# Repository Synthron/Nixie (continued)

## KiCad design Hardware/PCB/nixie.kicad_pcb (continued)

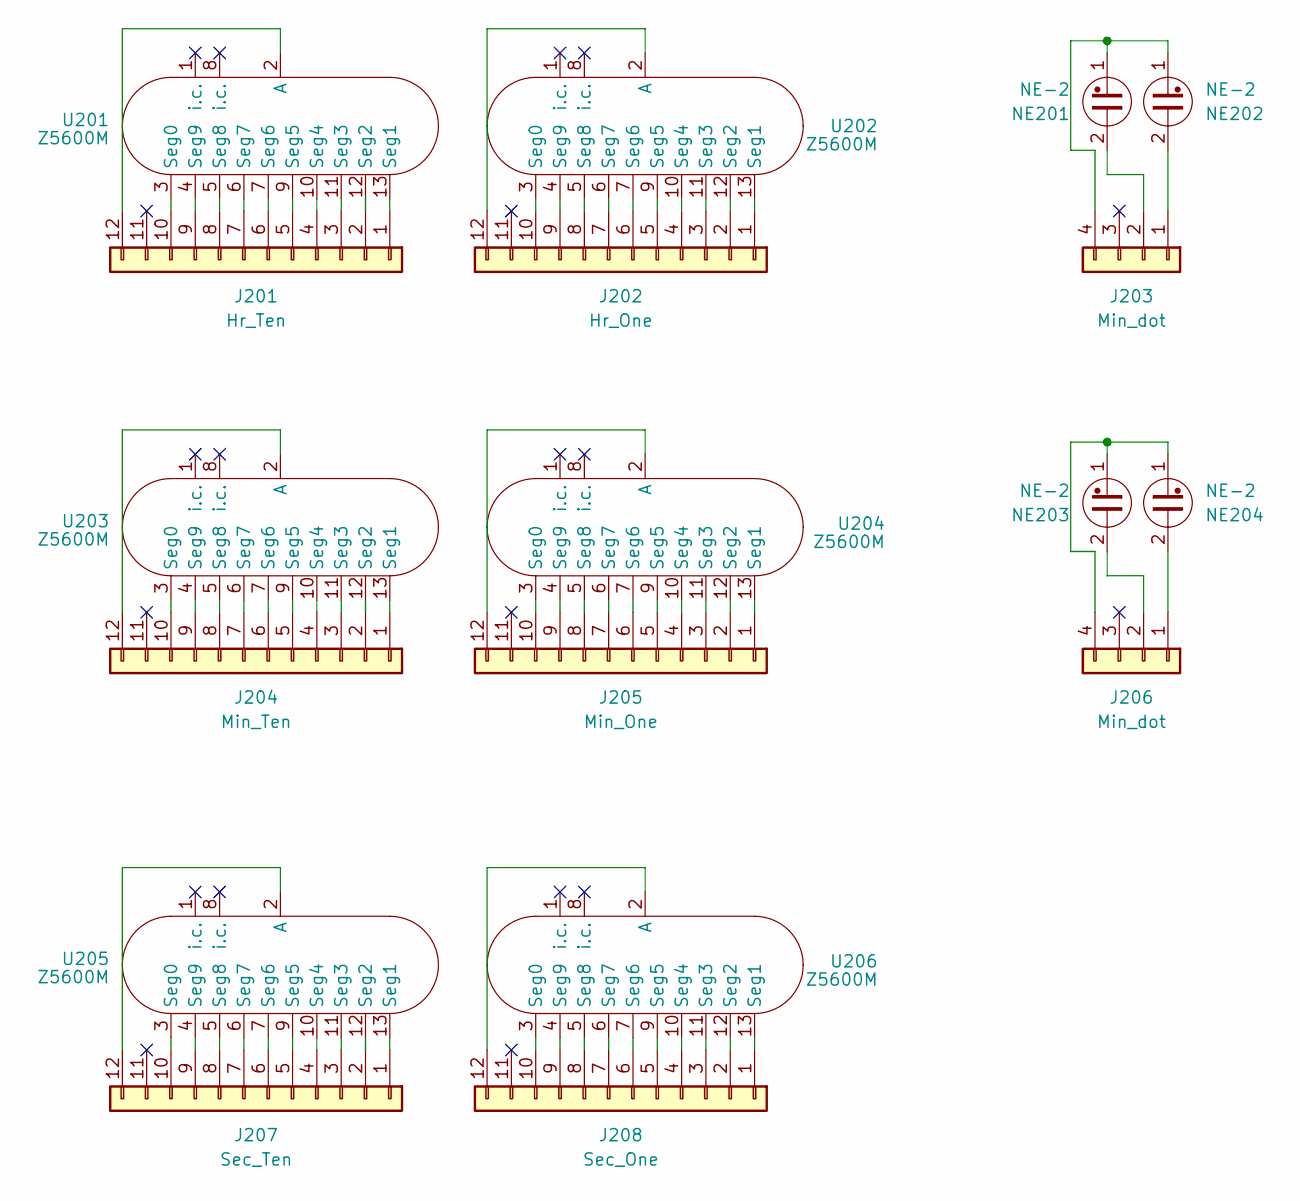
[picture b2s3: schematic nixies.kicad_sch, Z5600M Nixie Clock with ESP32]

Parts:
J201: Hr_Ten; PinSocket_1x12_P2.54mm_Vertical
J202: Hr_One; PinSocket_1x12_P2.54mm_Vertical
J203, J206: Min_dot; PinSocket_1x04_P2.54mm_Vertical
J204: Min_Ten; PinSocket_1x12_P2.54mm_Vertical
J205: Min_One; PinSocket_1x12_P2.54mm_Vertical
J207: Sec_Ten; PinSocket_1x12_P2.54mm_Vertical
J208: Sec_One; PinSocket_1x12_P2.54mm_Vertical
NE201, NE202, NE203, NE204: NE-2; Valve_Glimm
U201, U202, U203, U204, U205, U206: Z5600M; B13B

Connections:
unnamed: J201.1, U201.13 (Seg1)
unnamed: J201.2, U201.12 (Seg2)
unnamed: J201.3, U201.11 (Seg3)
unnamed: J201.4, U201.10 (Seg4)
unnamed: J201.5, U201.9 (Seg5)
unnamed: J201.6, U201.7 (Seg6)
unnamed: J201.7, U201.6 (Seg7)
unnamed: J201.8, U201.5 (Seg8)
unnamed: J201.9, U201.4 (Seg9)
unnamed: J201.10, U201.3 (Seg0)
unnamed: J201.12, U201.2 (A)
unnamed: J202.1, U202.13 (Seg1)
unnamed: J202.2, U202.12 (Seg2)
unnamed: J202.3, U202.11 (Seg3)
unnamed: J202.4, U202.10 (Seg4)
unnamed: J202.5, U202.9 (Seg5)
unnamed: J202.6, U202.7 (Seg6)
unnamed: J202.7, U202.6 (Seg7)
unnamed: J202.8, U202.5 (Seg8)
unnamed: J202.9, U202.4 (Seg9)
unnamed: J202.10, U202.3 (Seg0)
unnamed: J202.12, U202.2 (A)
unnamed: J203.1, NE202.2
unnamed: J203.2, NE201.2
unnamed: J203.4, NE201.1, NE202.1
unnamed: J204.1, U203.13 (Seg1)
unnamed: J204.2, U203.12 (Seg2)
unnamed: J204.3, U203.11 (Seg3)
unnamed: J204.4, U203.10 (Seg4)
unnamed: J204.5, U203.9 (Seg5)
unnamed: J204.6, U203.7 (Seg6)
unnamed: J204.7, U203.6 (Seg7)
unnamed: J204.8, U203.5 (Seg8)
unnamed: J204.9, U203.4 (Seg9)
unnamed: J204.10, U203.3 (Seg0)
unnamed: J204.12, U203.2 (A)
unnamed: J205.1, U204.13 (Seg1)
unnamed: J205.2, U204.12 (Seg2)
unnamed: J205.3, U204.11 (Seg3)
unnamed: J205.4, U204.10 (Seg4)
unnamed: J205.5, U204.9 (Seg5)
unnamed: J205.6, U204.7 (Seg6)
unnamed: J205.7, U204.6 (Seg7)
unnamed: J205.8, U204.5 (Seg8)
unnamed: J205.9, U204.4 (Seg9)
unnamed: J205.10, U204.3 (Seg0)
unnamed: J205.12, U204.2 (A)
unnamed: J206.1, NE204.2
unnamed: J206.2, NE203.2
unnamed: J206.4, NE203.1, NE204.1
unnamed: J207.1, U205.13 (Seg1)
unnamed: J207.2, U205.12 (Seg2)
unnamed: J207.3, U205.11 (Seg3)
unnamed: J207.4, U205.10 (Seg4)
unnamed: J207.5, U205.9 (Seg5)
unnamed: J207.6, U205.7 (Seg6)
unnamed: J207.7, U205.6 (Seg7)
unnamed: J207.8, U205.5 (Seg8)
unnamed: J207.9, U205.4 (Seg9)
unnamed: J207.10, U205.3 (Seg0)
unnamed: J207.12, U205.2 (A)
unnamed: J208.1, U206.13 (Seg1)
unnamed: J208.2, U206.12 (Seg2)
unnamed: J208.3, U206.11 (Seg3)
unnamed: J208.4, U206.10 (Seg4)
unnamed: J208.5, U206.9 (Seg5)
unnamed: J208.6, U206.7 (Seg6)
unnamed: J208.7, U206.6 (Seg7)
unnamed: J208.8, U206.5 (Seg8)
unnamed: J208.9, U206.4 (Seg9)
unnamed: J208.10, U206.3 (Seg0)
unnamed: J208.12, U206.2 (A)

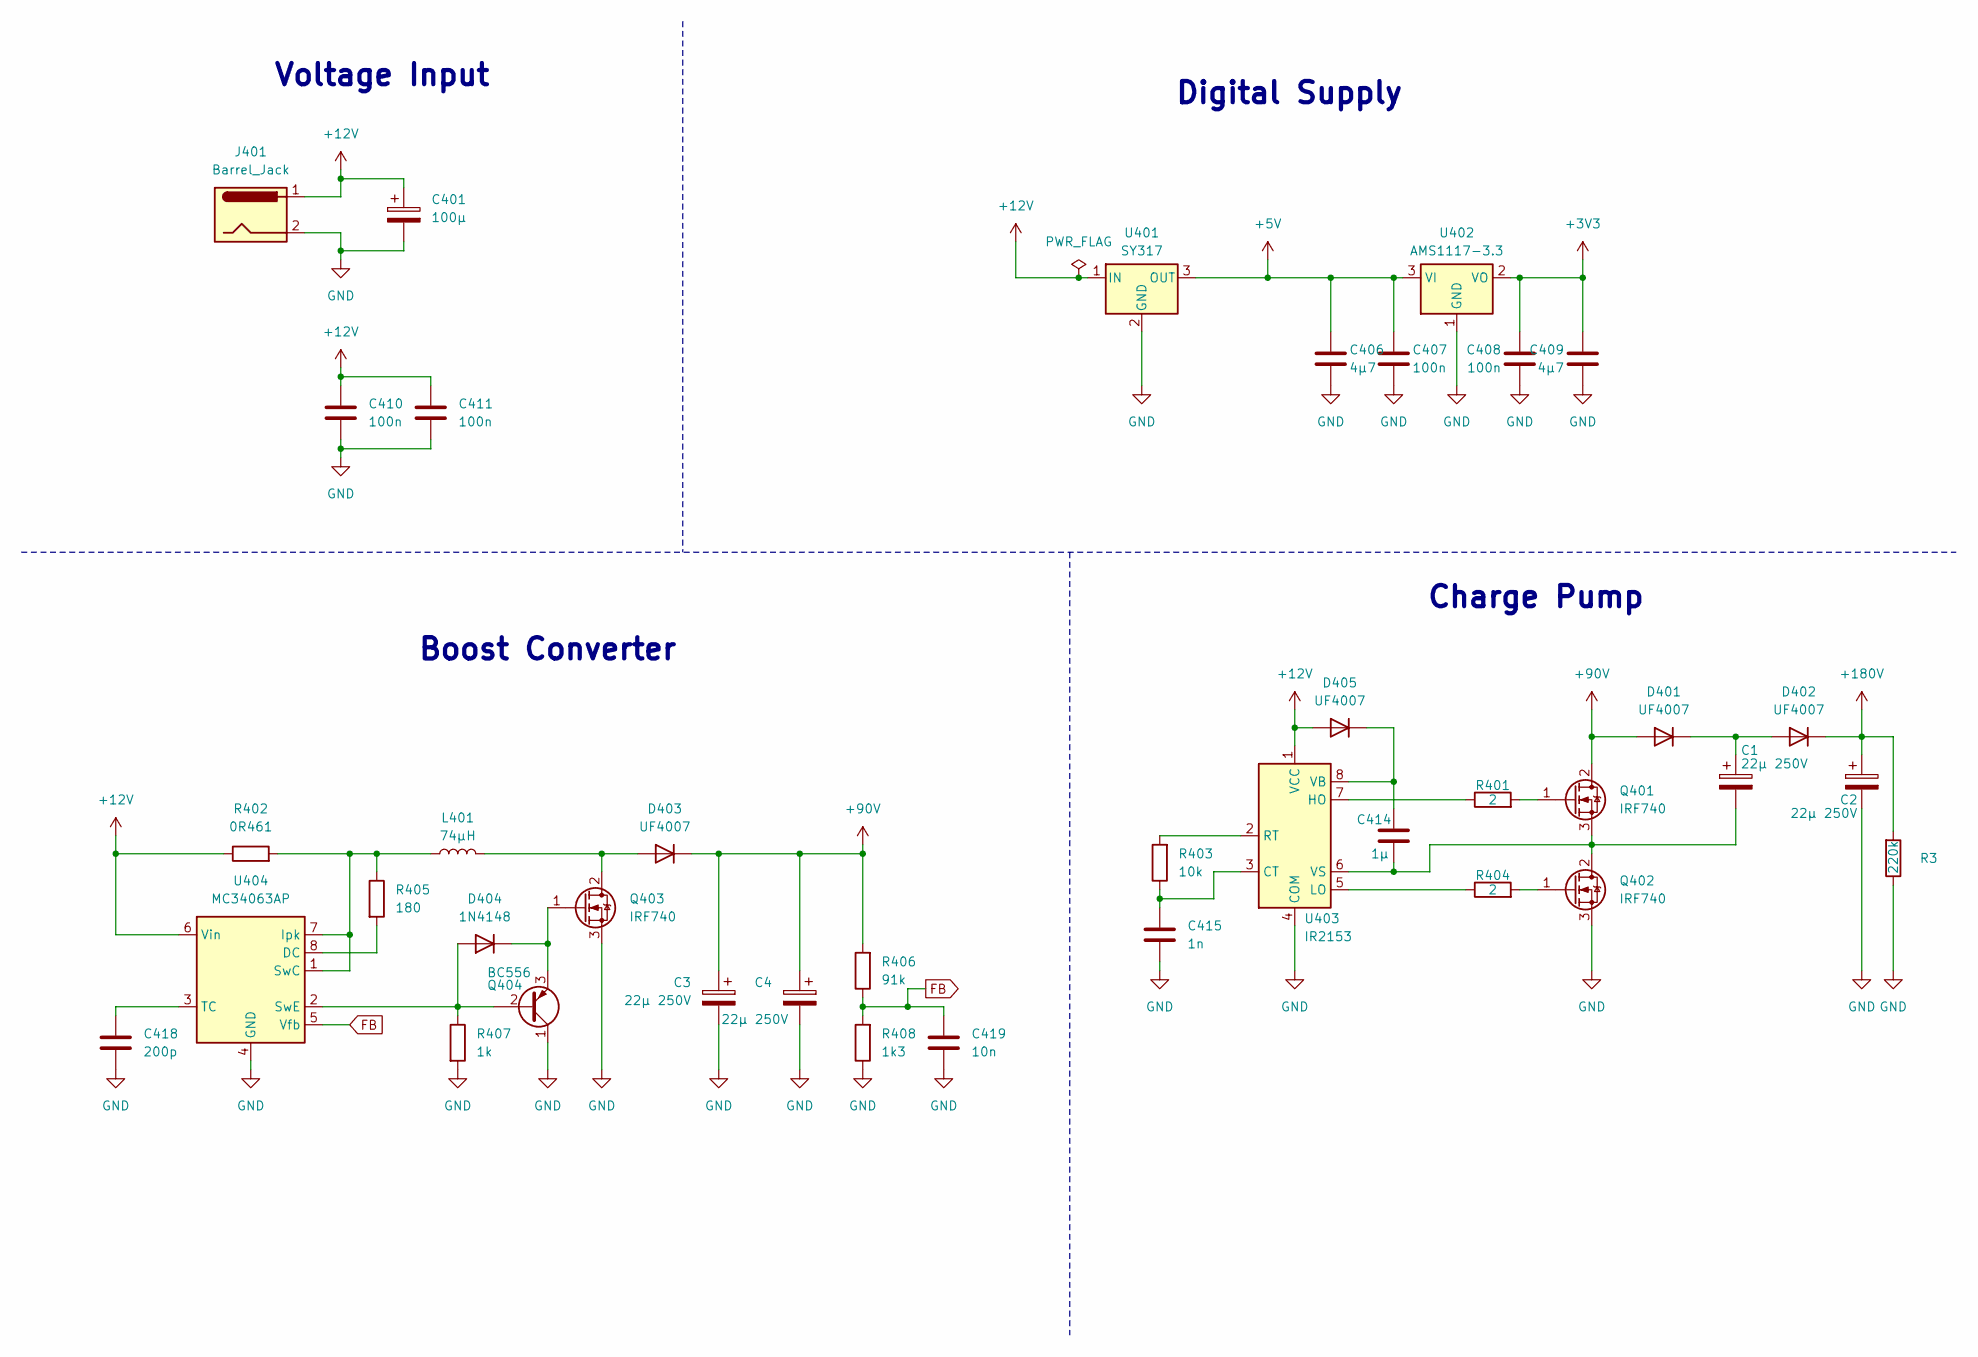
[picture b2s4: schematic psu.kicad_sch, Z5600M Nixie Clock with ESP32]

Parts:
C1, C2, C3, C4: 22µ 250V; CP_Radial_D10.0mm_P5.00mm
C401: 100µ; CP_Radial_D5.0mm_P2.50mm
C406, C409: 4µ7; C_0805_2012Metric
C407, C408: 100n; C_0805_2012Metric
C410, C411: 100n; C_Disc_D3.0mm_W1.6mm_P2.50mm
C414: 1µ; C_Rect_L18.0mm_W8.0mm_P15.00mm_FKS3_FKP3
C415: 1n; C_Disc_D3.0mm_W1.6mm_P2.50mm
C418: 200p; C_Disc_D3.0mm_W1.6mm_P2.50mm
C419: 10n; C_Disc_D3.0mm_W1.6mm_P2.50mm
D401, D402, D403, D405: UF4007; D_DO-41_SOD81_P10.16mm_Horizontal
D404: 1N4148; D_DO-35_SOD27_P7.62mm_Horizontal
J401: Barrel_Jack; BarrelJack_Horizontal
L401: 74µH; FT50-43
Q401, Q402, Q403: IRF740; TO-220-3_Vertical
Q404: BC556; TO-92
R3: 220k; R_Axial_DIN0207_L6.3mm_D2.5mm_P2.54mm_Vertical
R401, R404: 2; R_Axial_DIN0207_L6.3mm_D2.5mm_P2.54mm_Vertical
R402: 0R461; R_Axial_DIN0614_L14.3mm_D5.7mm_P5.08mm_Vertical
R403: 10k; R_Axial_DIN0207_L6.3mm_D2.5mm_P2.54mm_Vertical
R405: 180; R_Axial_DIN0207_L6.3mm_D2.5mm_P2.54mm_Vertical
R406: 91k; R_Axial_DIN0207_L6.3mm_D2.5mm_P2.54mm_Vertical
R407: 1k; R_Axial_DIN0207_L6.3mm_D2.5mm_P2.54mm_Vertical
R408: 1k3; R_Axial_DIN0207_L6.3mm_D2.5mm_P2.54mm_Vertical
U401: SY317; TO-220-3_Vertical
U402: AMS1117-3.3; SOT-223-3_TabPin2
U403: IR2153; DIP-8_W7.62mm
U404: MC34063AP; DIP-8_W7.62mm

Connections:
+3V3: C408.1, C409.1, U402.2 (VO); also elsewhere on the board
+5V: C406.1, C407.1, U401.3 (OUT), U402.3 (VI); also elsewhere on the board
+12V: C401.1, C410.1, C411.1, D405.2 (A), J401.1, R402.1, U401.1 (IN), U403.1 (VCC), U404.6 (Vin)
+90V: C3.1, C4.1, D401.2 (A), D403.1 (K), Q401.2 (D), R406.2
+180V: C2.1, D402.1 (K), R3.2; also elsewhere on the board
FB: C419.1, R406.1, R408.2, U404.5 (Vfb)
GND: C2.2, C3.2, C4.2, C401.2, C406.2, C407.2, C408.2, C409.2, C410.2, C411.2, C415.2, C418.2, C419.2, J401.2, Q402.3 (S), Q403.3 (S), Q404.1 (C), R3.1, R407.2, R408.1, U401.2 (GND), U402.1 (GND), U403.4 (COM), U404.4 (GND); also elsewhere on the board
unnamed: C1.1, D401.1 (K), D402.2 (A)
unnamed: D403.2 (A), L401.2, Q403.2 (D)
unnamed: D404.2 (A), Q404.2 (B), R407.1, U404.2 (SwE)
unnamed: D404.1 (K), Q403.1 (G), Q404.3 (E)
unnamed: C414.1, D405.1 (K), U403.8 (VB)
unnamed: Q401.1 (G), R401.2
unnamed: C1.2, C414.2, Q401.3 (S), Q402.2 (D), U403.6 (VS)
unnamed: Q402.1 (G), R404.2
unnamed: C415.1, R403.1, U403.3 (CT)
unnamed: R401.1, U403.7 (HO)
unnamed: R404.1, U403.5 (LO)
unnamed: R403.2, U403.2 (RT)
unnamed: R405.2, U404.8 (DC)
unnamed: L401.1, R402.2, R405.1, U404.1 (SwC), U404.7 (Ipk)
unnamed: C418.1, U404.3 (TC)

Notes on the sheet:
Digital Supply
Boost Converter
Charge Pump
Voltage Input

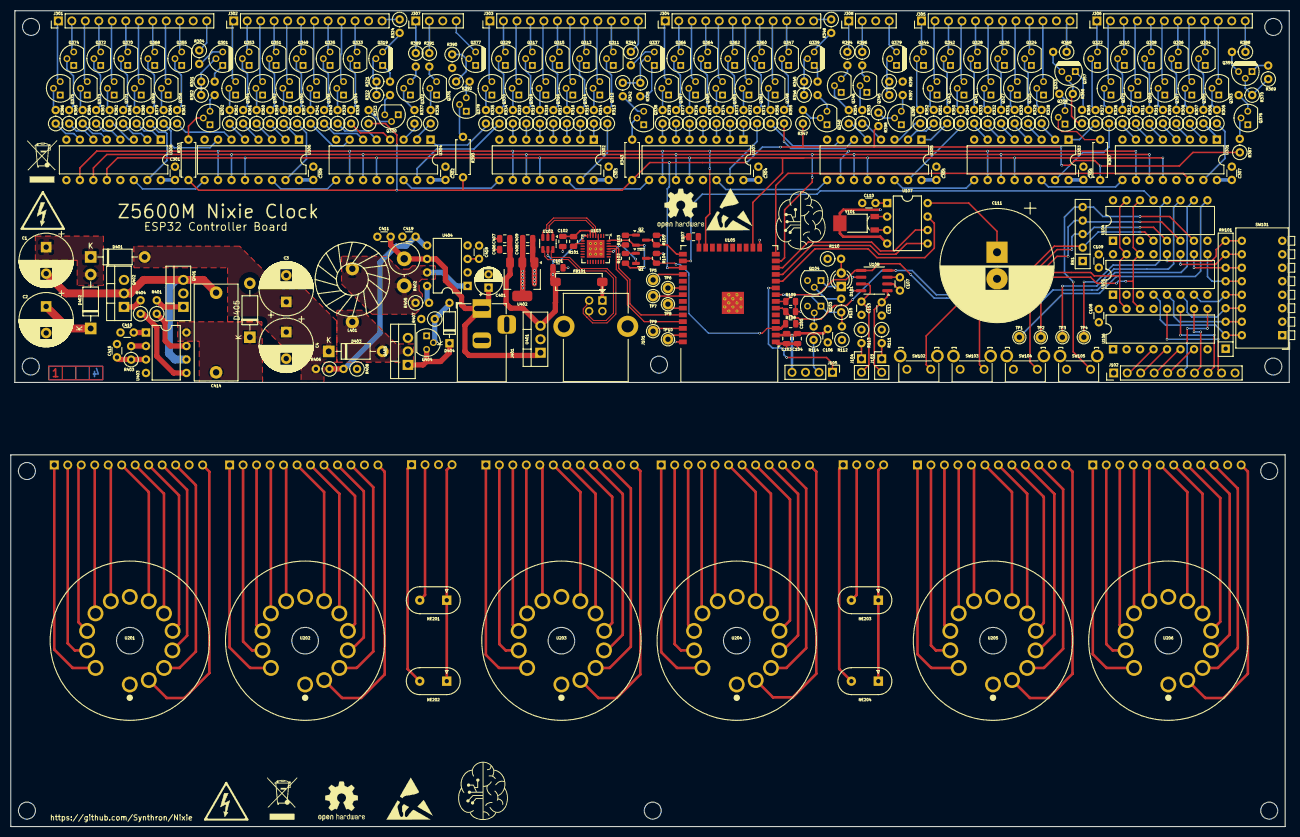
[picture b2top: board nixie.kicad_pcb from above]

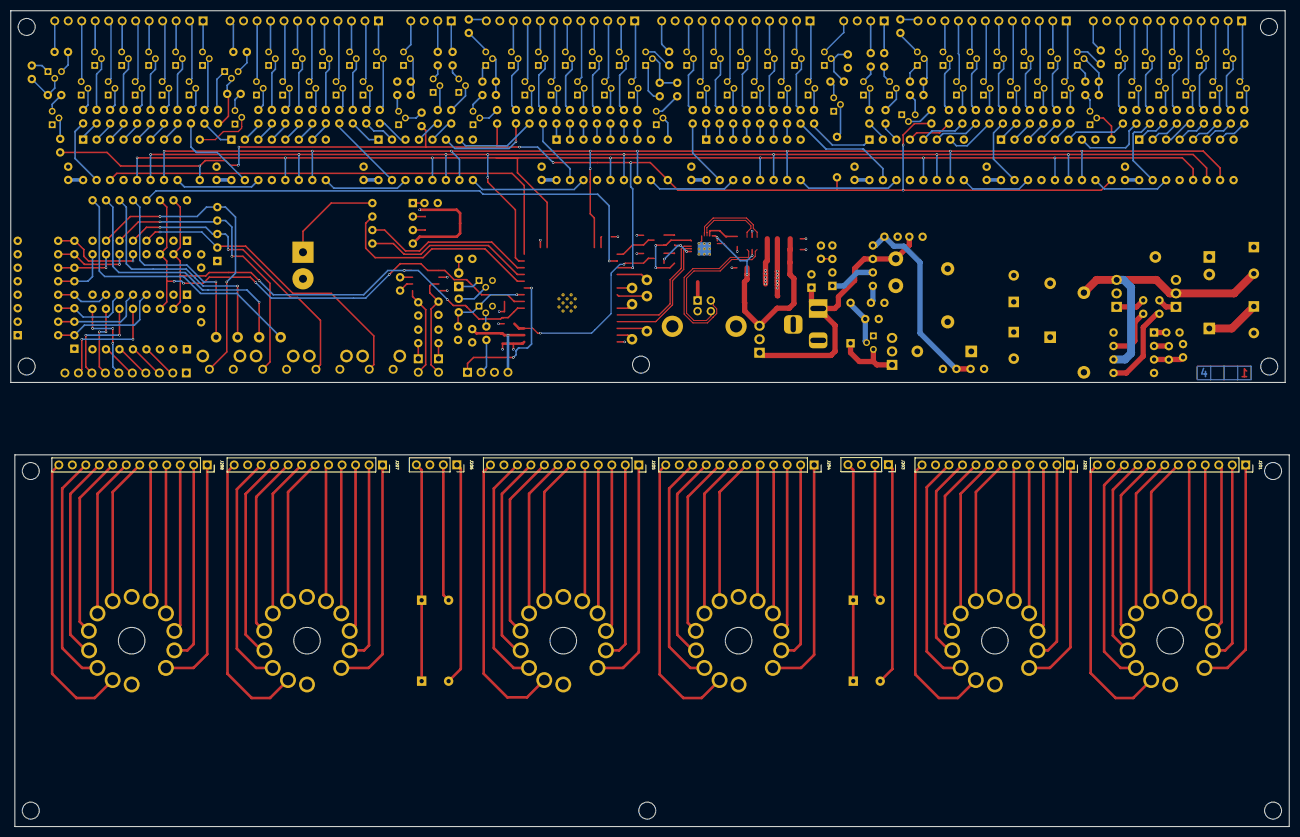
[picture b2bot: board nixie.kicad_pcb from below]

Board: 4 copper layers, 240.0 x 70.0 mm, 323 parts (8 on the bottom side), 406 nets.

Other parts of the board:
Ref**: Val**; ladder_4

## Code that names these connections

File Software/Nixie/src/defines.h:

#pragma once

// Compile-time constants (constexpr instead of #define so they are typed and
// scoped; each translation unit gets its own copy, which is fine for these).
constexpr bool FORMAT_SPIFFS_IF_FAILED = true;

// Pin Definitions
constexpr uint8_t PIN_INT   = 4;
constexpr uint8_t PIN_A2    = 5;
constexpr uint8_t PIN_DAT   = 12;
constexpr uint8_t PIN_RCLK  = 13;
constexpr uint8_t PIN_SCLK  = 14;
constexpr uint8_t PIN_SCLR  = 15;
constexpr uint8_t PIN_PWM   = 16;
constexpr uint8_t PIN_TP0   = 17;
constexpr uint8_t PIN_TP1   = 18;
constexpr uint8_t PIN_TP2   = 19;
constexpr uint8_t PIN_TP3   = 21;
constexpr uint8_t PIN_DCFSIG = 22;
constexpr uint8_t PIN_DCFEN = 23;
constexpr uint8_t PIN_RTCCLK = 25;
constexpr uint8_t PIN_RTCCE1 = 26;
constexpr uint8_t PIN_RTCIO = 27;
constexpr uint8_t PIN_SDA   = 34;
constexpr uint8_t PIN_SCL   = 35;

// I2C Addresses (int to match the Wire API's requestFrom/beginTransmission
// signatures and avoid overload ambiguity with int size arguments)
constexpr int ADDR_CONFIG = 0x20;
constexpr int ADDR_INPUT  = 0x21;
constexpr int ADDR_OUTPUT = 0x22;
constexpr int ADDR_ADC    = 0x68; // 0x01101000

constexpr int8_t T1_Offset = 5;
constexpr int8_t T2_Offset = 5;

// Debug output guard: only print to the USB serial when the USB strap is
// enabled (usb == true). Replaces the scattered `if(usb)` guards.
//   USB(...)   -> Serial.printf(...)
//   USBLN(...) -> Serial.println(...)
//   USBPR(...) -> Serial.print(...)
#define USB(...)   do { if (usb) Serial.printf(__VA_ARGS__); } while(0)
#define USBLN(...) do { if (usb) Serial.println(__VA_ARGS__); } while(0)
#define USBPR(...) do { if (usb) Serial.print(__VA_ARGS__); } while(0)

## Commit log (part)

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2024-09-16 first schematic draft
2024-09-17 schematic update
2024-09-18 Hardware Update Schematic Done Placement started
2024-09-22 PCB update finished placing and routing Cleanup Passes need to be done Silkscreen needs to be done
2024-09-23 PCB Update Silkscreen cleanup Layout Cleanup concept front plate
2024-09-29 small bugfix update
2024-10-03 reviewed version from thebrutzler
2024-10-03 remove backups
2024-10-05 Major Final Update Finalize design check all changes made during review revert back Footprint of Inductor Split PCB design into two projects add some functionality to ESP32 (Bootstrap and crystal)
2024-10-15 create dot spacer
2024-10-17 Initial Code Push Lot of functionality already implemented
2024-10-17 refactor code get tick from RTC optimize boot queue optimize button interface
2024-10-17 make PWM adjustable via buttons
2024-10-17 implement cyclic cycling of segments to counter cathode poisoning
2024-10-18 Small Code Update bugfix month number display implemented daily internal synchronization
2024-10-18 Bugfix RTC Oscillator Calibration
2024-10-18 Code Update RTC bugfix boot sequence trying to write to RTC when not initialized yet Cleanup of Class Function
2024-10-18 bugfix at synchronization funcion and cycle function
2024-10-18 Readme Update
2024-10-19 Bugfix external RTC Communication
2024-10-20 bugfix on setting rtc
2024-10-20 implement automatic Daylight Savings Time Calculation for Germany
2024-10-20 bugfixes of month calculation, DST calculation, boot strapping
2024-10-20 crude 3d printed spacers with isolation for pin headers
2024-10-21 add FreeCAD files
2024-10-23 Code Update Implement ADC read Implement PT100 Display Implement LDR & automatic dimming
2024-10-25 bugfix in DST calculation
2024-10-25 disable debug message
2024-12-15 Optimizations disable DST do number cycling every hour for 2 minutes to fix cathode poisoning issue
2025-01-03 small code update bugfix for wrong month display added more filament cycle time for cathode poisoning prevention
2025-06-19 add quick fix for DST, press MODE button to toggle DST
